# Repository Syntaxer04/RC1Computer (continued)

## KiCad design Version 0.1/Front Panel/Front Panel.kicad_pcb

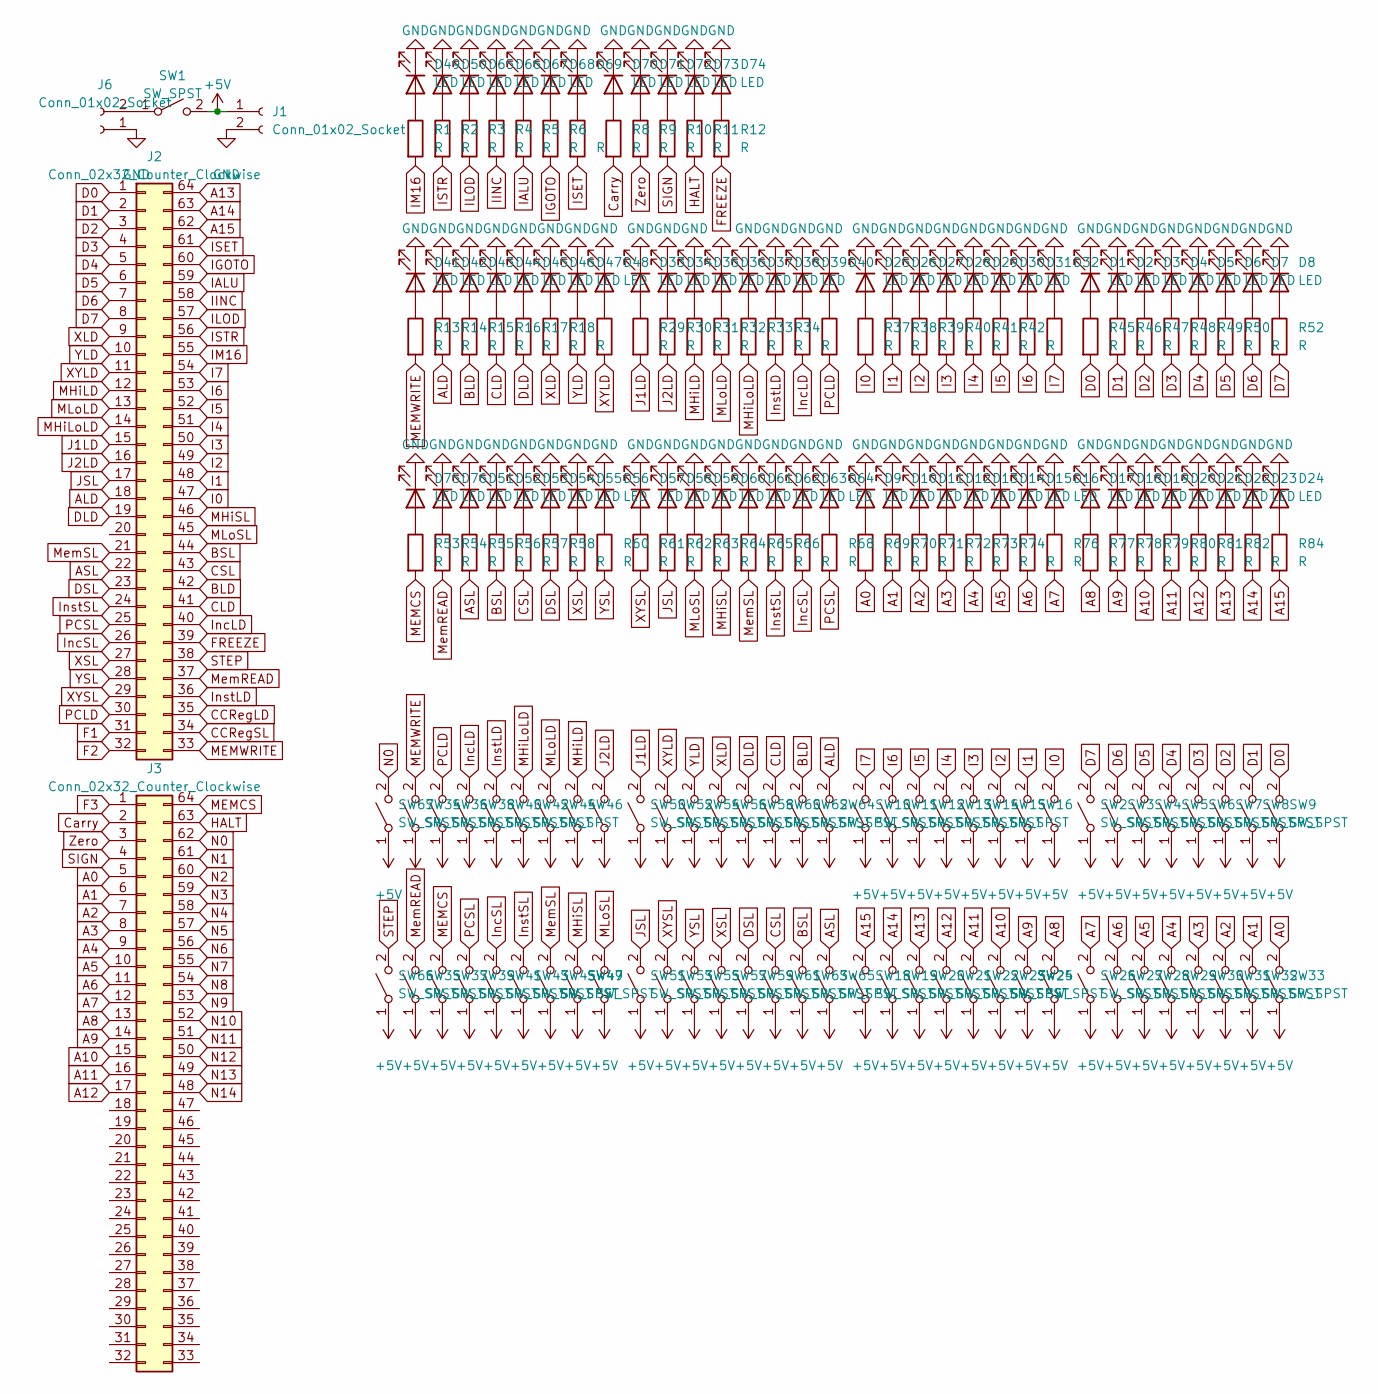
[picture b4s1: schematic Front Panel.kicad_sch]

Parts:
D1, D2, D3, D4, D5, D6, D7, D8, D9, D10, D11, D12, D13, D14, D15, D16, D17, D18, D19, D20, D21, D22, D23, D24, D25, D26, D27, D28, D29, D30, D31, D32, D33, D34, D35, D36, D37, D38, D39, D40, D41, D42, D43, D44, D45, D46, D47, D48, D49, D50, D51, D52, D53, D54, D55, D56, D57, D58, D59, D60, D61, D62, D63, D64, D65, D66, D67, D68, D69, D70, D71, D72, D73, D74, D75, D76: LED; LED_D8.0mm
J1, J6: Conn_01x02_Socket; JWT_A3963_1x02_P3.96mm_Vertical
J2, J3: Conn_02x32_Counter_Clockwise; IDC-Header_2x32_P2.54mm_Vertical
R1, R2, R3, R4, R5, R6, R7, R8, R9, R10, R11, R12, R13, R14, R15, R16, R17, R18, R19, R20, R29, R30, R31, R32, R33, R34, R35, R36, R37, R38, R39, R40, R41, R42, R43, R44, R45, R46, R47, R48, R49, R50, R51, R52, R53, R54, R55, R56, R57, R58, R59, R60, R61, R62, R63, R64, R65, R66, R67, R68, R69, R70, R71, R72, R73, R74, R75, R76, R77, R78, R79, R80, R81, R82, R83, R84: R; R_Axial_DIN0204_L3.6mm_D1.6mm_P2.54mm_Vertical
SW1, SW2, SW3, SW4, SW5, SW6, SW7, SW8, SW9, SW10, SW11, SW12, SW13, SW14, SW15, SW16, SW17, SW18, SW19, SW20, SW21, SW22, SW23, SW24, SW25, SW26, SW27, SW28, SW29, SW30, SW31, SW32, SW33, SW34, SW35, SW36, SW37, SW38, SW39, SW40, SW41, SW42, SW43, SW44, SW45, SW46, SW47, SW48, SW49, SW50, SW51, SW52, SW53, SW54, SW55, SW56, SW57, SW58, SW59, SW60, SW61, SW62, SW63, SW64, SW65, SW66, SW67: SW_SPST; Switches

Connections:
+5V: J1.1, SW1.2 (B), SW2.1 (A), SW3.1 (A), SW4.1 (A), SW5.1 (A), SW6.1 (A), SW7.1 (A), SW8.1 (A), SW9.1 (A), SW10.1 (A), SW11.1 (A), SW12.1 (A), SW13.1 (A), SW14.1 (A), SW15.1 (A), SW16.1 (A), SW17.1 (A), SW18.1 (A), SW19.1 (A), SW20.1 (A), SW21.1 (A), SW22.1 (A), SW23.1 (A), SW24.1 (A), SW25.1 (A), SW26.1 (A), SW27.1 (A), SW28.1 (A), SW29.1 (A), SW30.1 (A), SW31.1 (A), SW32.1 (A), SW33.1 (A), SW34.1 (A), SW35.1 (A), SW36.1 (A), SW37.1 (A), SW38.1 (A), SW39.1 (A), SW40.1 (A), SW41.1 (A), SW42.1 (A), SW43.1 (A), SW44.1 (A), SW45.1 (A), SW46.1 (A), SW47.1 (A), SW48.1 (A), SW49.1 (A), SW50.1 (A), SW51.1 (A), SW52.1 (A), SW53.1 (A), SW54.1 (A), SW55.1 (A), SW56.1 (A), SW57.1 (A), SW58.1 (A), SW59.1 (A), SW60.1 (A), SW61.1 (A), SW62.1 (A), SW63.1 (A), SW64.1 (A), SW65.1 (A), SW66.1 (A), SW67.1 (A)
A0: J3.5, R69.2, SW33.2 (B)
A1: J3.6, R70.2, SW32.2 (B)
A2: J3.7, R71.2, SW31.2 (B)
A3: J3.8, R72.2, SW30.2 (B)
A4: J3.9, R73.2, SW29.2 (B)
A5: J3.10, R74.2, SW28.2 (B)
A6: J3.11, R75.2, SW27.2 (B)
A7: J3.12, R76.2, SW26.2 (B)
A8: J3.13, R77.2, SW25.2 (B)
A9: J3.14, R78.2, SW24.2 (B)
A10: J3.15, R79.2, SW23.2 (B)
A11: J3.16, R80.2, SW22.2 (B)
A12: J3.17, R81.2, SW21.2 (B)
A13: J2.64, R82.2, SW20.2 (B)
A14: J2.63, R83.2, SW19.2 (B)
A15: J2.62, R84.2, SW18.2 (B)
ALD: J2.18, R14.2, SW64.2 (B)
ASL: J2.22, R55.2, SW65.2 (B)
BLD: J2.42, R15.2, SW62.2 (B)
BSL: J2.44, R56.2, SW63.2 (B)
CCRegLD: J2.35
CCRegSL: J2.34
CLD: J2.41, R16.2, SW60.2 (B)
CSL: J2.43, R57.2, SW61.2 (B)
Carry: J3.2, R8.2
D0: J2.1, R45.2, SW9.2 (B)
D1: J2.2, R46.2, SW8.2 (B)
D2: J2.3, R47.2, SW7.2 (B)
D3: J2.4, R48.2, SW6.2 (B)
D4: J2.5, R49.2, SW5.2 (B)
D5: J2.6, R50.2, SW4.2 (B)
D6: J2.7, R51.2, SW3.2 (B)
D7: J2.8, R52.2, SW2.2 (B)
DLD: J2.19, R17.2, SW58.2 (B)
DSL: J2.23, R58.2, SW59.2 (B)
F1: J2.31
F2: J2.32
F3: J3.1
FREEZE: J2.39, R12.2
GND: D1.1 (K), D2.1 (K), D3.1 (K), D4.1 (K), D5.1 (K), D6.1 (K), D7.1 (K), D8.1 (K), D9.1 (K), D10.1 (K), D11.1 (K), D12.1 (K), D13.1 (K), D14.1 (K), D15.1 (K), D16.1 (K), D17.1 (K), D18.1 (K), D19.1 (K), D20.1 (K), D21.1 (K), D22.1 (K), D23.1 (K), D24.1 (K), D25.1 (K), D26.1 (K), D27.1 (K), D28.1 (K), D29.1 (K), D30.1 (K), D31.1 (K), D32.1 (K), D33.1 (K), D34.1 (K), D35.1 (K), D36.1 (K), D37.1 (K), D38.1 (K), D39.1 (K), D40.1 (K), D41.1 (K), D42.1 (K), D43.1 (K), D44.1 (K), D45.1 (K), D46.1 (K), D47.1 (K), D48.1 (K), D49.1 (K), D50.1 (K), D51.1 (K), D52.1 (K), D53.1 (K), D54.1 (K), D55.1 (K), D56.1 (K), D57.1 (K), D58.1 (K), D59.1 (K), D60.1 (K), D61.1 (K), D62.1 (K), D63.1 (K), D64.1 (K), D65.1 (K), D66.1 (K), D67.1 (K), D68.1 (K), D69.1 (K), D70.1 (K), D71.1 (K), D72.1 (K), D73.1 (K), D74.1 (K), D75.1 (K), D76.1 (K), J1.2, J6.1
HALT: J3.63, R11.2
I0: J2.47, R37.2, SW17.2 (B)
I1: J2.48, R38.2, SW16.2 (B)
I2: J2.49, R39.2, SW15.2 (B)
I3: J2.50, R40.2, SW14.2 (B)
I4: J2.51, R41.2, SW13.2 (B)
I5: J2.52, R42.2, SW12.2 (B)
I6: J2.53, R43.2, SW11.2 (B)
I7: J2.54, R44.2, SW10.2 (B)
IALU: J2.59, R5.2
IGOTO: J2.60, R6.2
IINC: J2.58, R4.2
ILOD: J2.57, R3.2
IM16: J2.55, R1.2
ISET: J2.61, R7.2
ISTR: J2.56, R2.2
IncLD: J2.40, R35.2, SW38.2 (B)
IncSL: J2.26, R67.2, SW41.2 (B)
InstLD: J2.36, R34.2, SW40.2 (B)
InstSL: J2.24, R66.2, SW43.2 (B)
J1LD: J2.15, R29.2, SW50.2 (B)
J2LD: J2.16, R30.2, SW48.2 (B)
JSL: J2.17, R62.2, SW51.2 (B)
MEMCS: J3.64, R53.2, SW37.2 (B)
MEMWRITE: J2.33, R13.2, SW34.2 (B)
MHiLD: J2.12, R31.2, SW46.2 (B)
MHiLoLD: J2.14, R33.2, SW42.2 (B)
MHiSL: J2.46, R64.2, SW47.2 (B)
MLoLD: J2.13, R32.2, SW44.2 (B)
MLoSL: J2.45, R63.2, SW49.2 (B)
MemREAD: J2.37, R54.2, SW35.2 (B)
MemSL: J2.21, R65.2, SW45.2 (B)
N0: J3.62, SW67.2 (B)
N1: J3.61
N2: J3.60
N3: J3.59
N4: J3.58
N5: J3.57
N6: J3.56
N7: J3.55
N8: J3.54
N9: J3.53
N10: J3.52
N11: J3.51
N12: J3.50
N13: J3.49
N14: J3.48
unnamed: D1.2 (A), R45.1
unnamed: D2.2 (A), R46.1
unnamed: D3.2 (A), R47.1
unnamed: D4.2 (A), R48.1
unnamed: D5.2 (A), R49.1
unnamed: D6.2 (A), R50.1
unnamed: D7.2 (A), R51.1
unnamed: D8.2 (A), R52.1
unnamed: D9.2 (A), R69.1
unnamed: D10.2 (A), R70.1
unnamed: D11.2 (A), R71.1
unnamed: D12.2 (A), R72.1
unnamed: D13.2 (A), R73.1
unnamed: D14.2 (A), R74.1
unnamed: D15.2 (A), R75.1
unnamed: D16.2 (A), R76.1
unnamed: D17.2 (A), R77.1
unnamed: D18.2 (A), R78.1
unnamed: D19.2 (A), R79.1
unnamed: D20.2 (A), R80.1
unnamed: D21.2 (A), R81.1
unnamed: D22.2 (A), R82.1
unnamed: D23.2 (A), R83.1
unnamed: D24.2 (A), R84.1
unnamed: D25.2 (A), R37.1
unnamed: D26.2 (A), R38.1
unnamed: D27.2 (A), R39.1
unnamed: D28.2 (A), R40.1
unnamed: D29.2 (A), R41.1
unnamed: D30.2 (A), R42.1
unnamed: D31.2 (A), R43.1
unnamed: D32.2 (A), R44.1
unnamed: D33.2 (A), R29.1
unnamed: D34.2 (A), R30.1
unnamed: D35.2 (A), R31.1
unnamed: D36.2 (A), R32.1
unnamed: D37.2 (A), R33.1
unnamed: D38.2 (A), R34.1
unnamed: D39.2 (A), R35.1
unnamed: D40.2 (A), R36.1
unnamed: D41.2 (A), R13.1
unnamed: D42.2 (A), R14.1
unnamed: D43.2 (A), R15.1
unnamed: D44.2 (A), R16.1
unnamed: D45.2 (A), R17.1
unnamed: D46.2 (A), R18.1
unnamed: D47.2 (A), R19.1
unnamed: D48.2 (A), R20.1
unnamed: D49.2 (A), R1.1
unnamed: D50.2 (A), R2.1
unnamed: D51.2 (A), R55.1
unnamed: D52.2 (A), R56.1
unnamed: D53.2 (A), R57.1
unnamed: D54.2 (A), R58.1
unnamed: D55.2 (A), R59.1
unnamed: D56.2 (A), R60.1
unnamed: D57.2 (A), R61.1
unnamed: D58.2 (A), R62.1
unnamed: D59.2 (A), R63.1
unnamed: D60.2 (A), R64.1
unnamed: D61.2 (A), R65.1
unnamed: D62.2 (A), R66.1
unnamed: D63.2 (A), R67.1
unnamed: D64.2 (A), R68.1
unnamed: D65.2 (A), R3.1
unnamed: D66.2 (A), R4.1
unnamed: D67.2 (A), R5.1
unnamed: D68.2 (A), R6.1
unnamed: D69.2 (A), R7.1
unnamed: D70.2 (A), R8.1
unnamed: D71.2 (A), R9.1
unnamed: D72.2 (A), R10.1
unnamed: D73.2 (A), R11.1
unnamed: D74.2 (A), R12.1
unnamed: D75.2 (A), R53.1
unnamed: D76.2 (A), R54.1
unnamed: J6.2, SW1.1 (A)
PCLD: J2.30, R36.2, SW36.2 (B)
PCSL: J2.25, R68.2, SW39.2 (B)
SIGN: J3.4, R10.2
STEP: J2.38, SW66.2 (B)
XLD: J2.9, R18.2, SW56.2 (B)
XSL: J2.27, R59.2, SW57.2 (B)
XYLD: J2.11, R20.2, SW52.2 (B)
XYSL: J2.29, R61.2, SW53.2 (B)
YLD: J2.10, R19.2, SW54.2 (B)
YSL: J2.28, R60.2, SW55.2 (B)
Zero: J3.3, R9.2

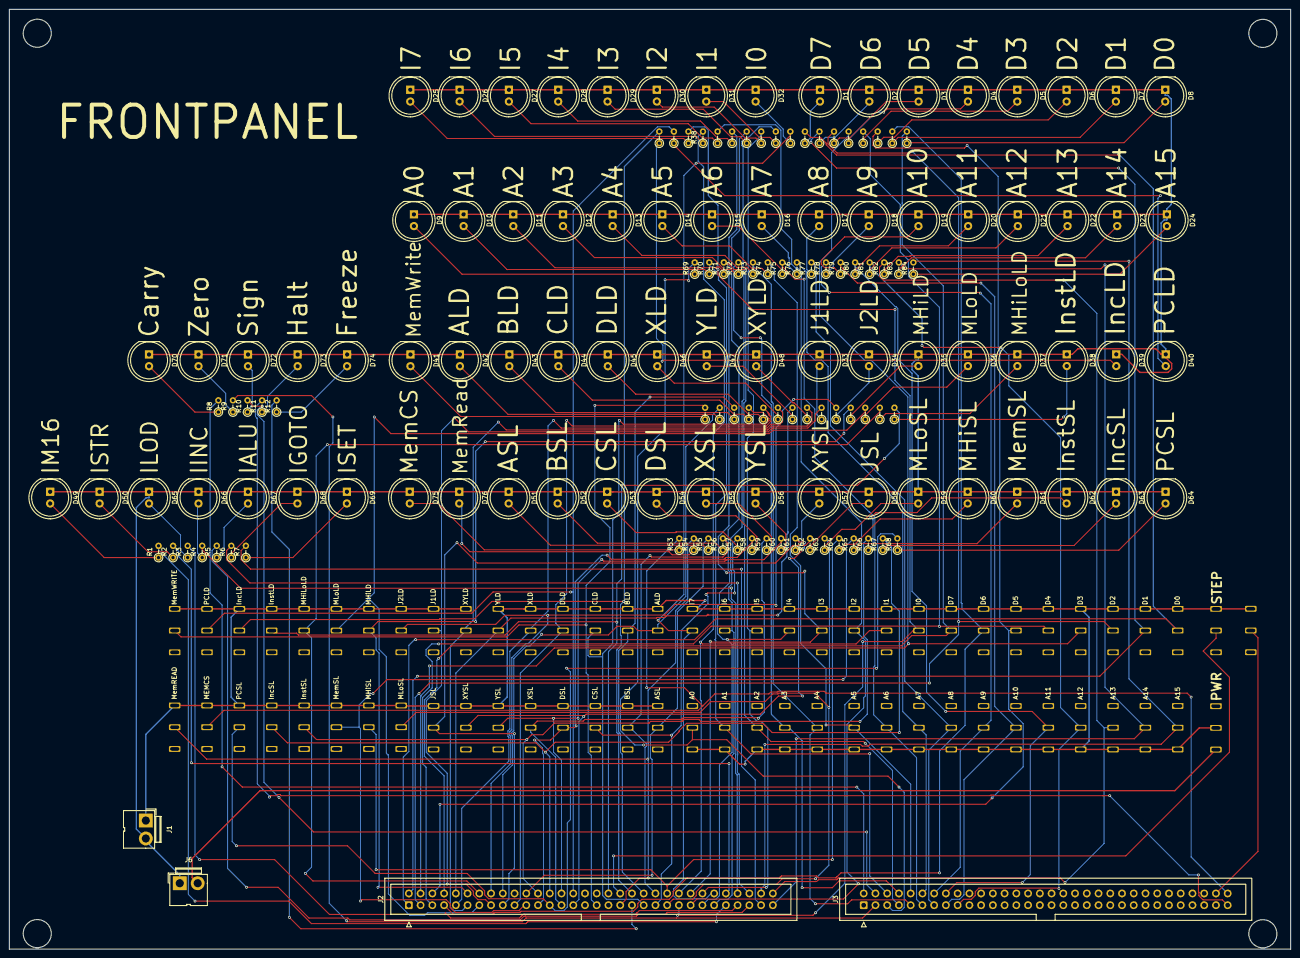
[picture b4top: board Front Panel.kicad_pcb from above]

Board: 2 copper layers, 277.2 x 203.3 mm, 223 parts (0 on the bottom side), 157 nets.

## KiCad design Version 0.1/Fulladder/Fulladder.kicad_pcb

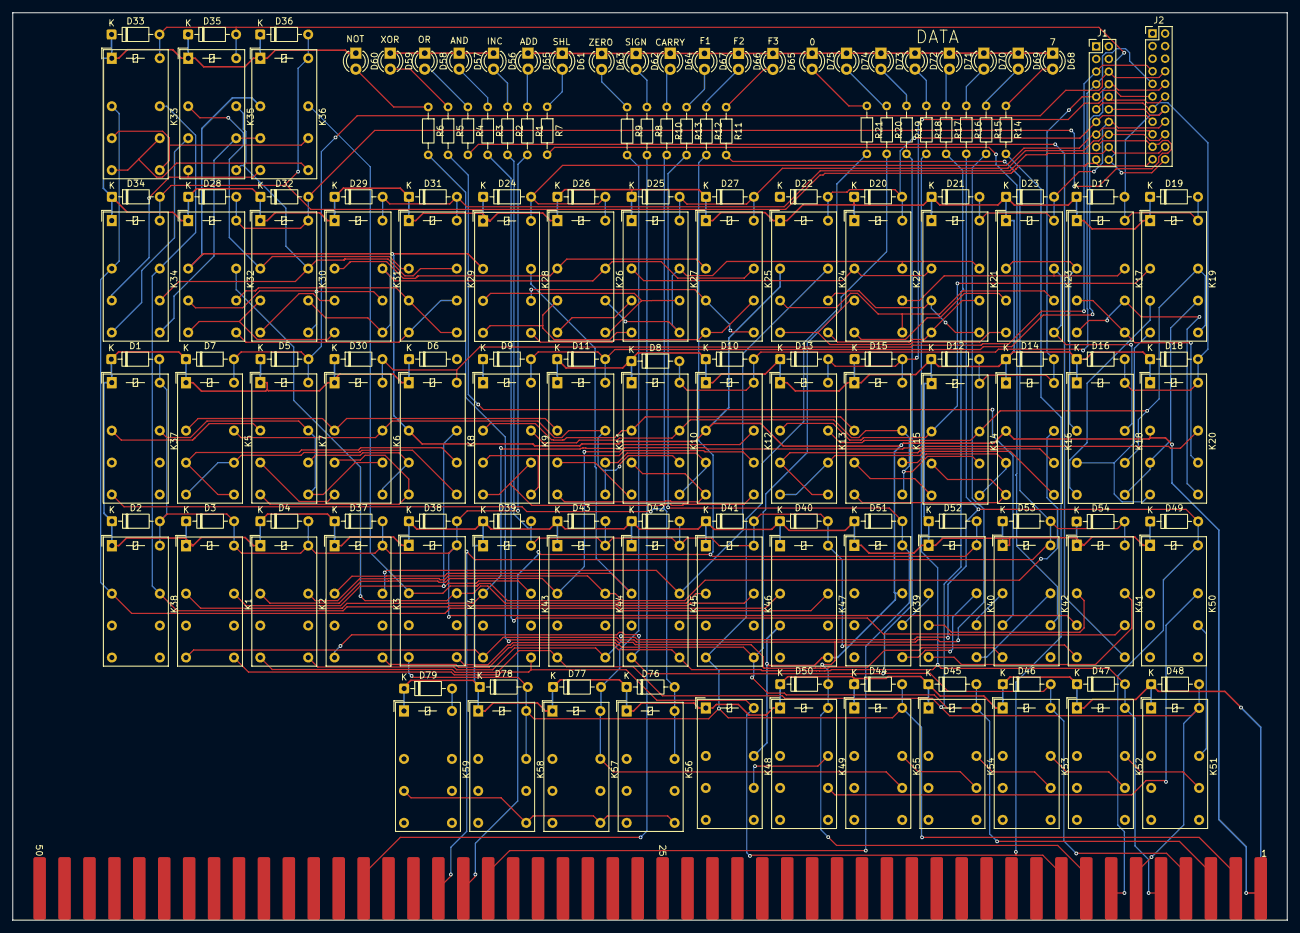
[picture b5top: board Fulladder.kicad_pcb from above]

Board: 2 copper layers, 202.5 x 144.2 mm, 162 parts (0 on the bottom side), 142 nets.

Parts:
D1, D2, D3, D4, D5, D6, D7, D8, D9, D10, D11, D12, D13, D14, D15, D16, D17, D18, D19, D20, D21, D22, D23, D24, D25, D26, D27, D28, D29, D30, D31, D32, D33, D34, D35, D36, D37, D38, D39, D40, D41, D42, D43, D44, D45, D46, D47, D48, D49, D50, D51, D52, D53, D54, D76, D77, D78, D79: 1N914; D_DO-35_SOD27_P7.62mm_Horizontal
D55, D56, D57, D58, D59, D60, D61, D62, D63, D64, D65, D66, D67, D68, D69, D70, D71, D72, D73, D74, D75: LED; LED_D3.0mm
J1: Conn_02x10_Odd_Even; PinHeader_2x10_P2.00mm_Vertical
J2: Conn_02x11_Odd_Even; PinHeader_2x11_P2.00mm_Vertical
K1, K2, K3, K4, K5, K6, K7, K8, K9, K10, K11, K12, K13, K14, K15, K16, K17, K18, K19, K20, K21, K22, K23, K24, K25, K26, K27, K28, K29, K30, K31, K32, K33, K34, K35, K36, K37, K38, K39, K40, K41, K42, K43, K44, K45, K46, K47, K48, K49, K50, K51, K52, K53, K54, K55, K56, K57, K58, K59: HK19F-DCxxV-SHC; Relay_DPDT_Finder_30.22
R1, R2, R3, R4, R5, R6, R7, R8, R9, R10, R11, R12, R13, R14, R15, R16, R17, R18, R19, R20, R21: R; R_Axial_DIN0204_L3.6mm_D1.6mm_P7.62mm_Horizontal
U1: Conn_RC_Male_100

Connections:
CCLD: D79.2 (A), K59.A2
Carry: D76.2 (A), K37.14, K56.21, K56.A2, R10.2
GND: D1.1 (K), D2.1 (K), D3.1 (K), D4.1 (K), D5.1 (K), D6.1 (K), D7.1 (K), D8.1 (K), D10.1 (K), D11.1 (K), D12.1 (K), D13.1 (K), D14.1 (K), D15.1 (K), D16.1 (K), D17.1 (K), D18.1 (K), D19.1 (K), D20.1 (K), D21.1 (K), D23.1 (K), D24.1 (K), D25.1 (K), D26.1 (K), D27.1 (K), D28.1 (K), D29.1 (K), D30.1 (K), D31.1 (K), D32.1 (K), D33.1 (K), D34.1 (K), D35.1 (K), D36.1 (K), D37.1 (K), D38.1 (K), D39.1 (K), D40.1 (K), D41.1 (K), D42.1 (K), D43.1 (K), D44.1 (K), D45.1 (K), D46.1 (K), D47.1 (K), D48.1 (K), D49.1 (K), D50.1 (K), D51.1 (K), D52.1 (K), D53.1 (K), D54.1 (K), D55.1 (K), D56.1 (K), D57.1 (K), D58.1 (K), D59.1 (K), D60.1 (K), D61.1 (K), D62.1 (K), D63.1 (K), D64.1 (K), D65.1 (K), D66.1 (K), D67.1 (K), D68.1 (K), D69.1 (K), D70.1 (K), D71.1 (K), D72.1 (K), D73.1 (K), D74.1 (K), D75.1 (K), D76.1 (K), D77.1 (K), D78.1 (K), D79.1 (K), K1.A1, K2.A1, K3.A1, K4.A1, K5.A1, K6.A1, K7.A1, K8.A1, K10.A1, K11.A1, K12.A1, K13.A1, K14.A1, K15.A1, K16.A1, K17.A1, K18.A1, K19.A1, K20.A1, K21.A1, K22.A1, K23.A1, K24.A1, K25.A1, K26.A1, K27.A1, K28.A1, K29.A1, K30.A1, K31.A1, K32.A1, K33.A1, K34.A1, K35.A1, K36.A1, K37.A1, K38.A1, K39.A1, K40.A1, K41.A1, K42.A1, K43.A1, K44.A1, K45.A1, K46.A1, K47.A1, K48.A1, K49.A1, K50.A1, K51.A1, K52.A1, K53.A1, K54.A1, K55.A1, K56.A1, K57.A1, K58.A1, K59.A1, U1.51 (GND)
unnamed: D1.2 (A), D2.2 (A), D3.2 (A), D4.2 (A), D37.2 (A), D38.2 (A), K1.A2, K2.A2, K3.A2, K4.A2, K37.A2, K38.A2, K41.12, R1.2
unnamed: D5.2 (A), D7.2 (A), J1.6, J2.8, K5.A2, K7.A2
unnamed: D9.1 (K), K9.A1
unnamed: D8.2 (A), D10.2 (A), J1.7, J2.9, K10.A2, K12.A2
unnamed: D9.2 (A), D11.2 (A), J1.8, J2.10, K9.A2, K11.A2
unnamed: D12.2 (A), D14.2 (A), J1.9, J2.11, K14.A2, K16.A2
unnamed: D13.2 (A), D15.2 (A), J1.10, J2.12, K13.A2, K15.A2
unnamed: D16.2 (A), D18.2 (A), J1.11, J2.13, K18.A2, K20.A2
unnamed: D17.2 (A), D19.2 (A), J1.12, J2.14, K17.A2, K19.A2
unnamed: D20.2 (A), D22.2 (A), J1.13, J2.15, K22.A2, K24.A2
unnamed: D21.2 (A), D23.2 (A), J1.14, J2.16, K21.A2, K23.A2
unnamed: D24.2 (A), D26.2 (A), J1.15, J2.17, K26.A2, K28.A2
unnamed: D25.2 (A), D27.2 (A), J1.16, J2.18, K25.A2, K27.A2
unnamed: D28.2 (A), D32.2 (A), J1.17, J2.19, K30.A2, K32.A2
unnamed: D29.2 (A), D31.2 (A), J1.18, J2.20, K29.A2, K31.A2
unnamed: D30.2 (A), J1.5, J2.7, K6.A2, K8.A2
unnamed: D33.2 (A), D35.2 (A), J1.20, J2.22, K33.A2, K35.A2
unnamed: D34.2 (A), D36.2 (A), J1.19, J2.21, K34.A2, K36.A2
unnamed: D39.2 (A), D40.2 (A), D41.2 (A), D42.2 (A), D43.2 (A), K41.14, K43.A2, K44.A2, K45.A2, K46.A2, K47.A2, R2.2
unnamed: D45.2 (A), K4.24, K46.24, K54.A2, R20.2, U1.3 (D1)
unnamed: D46.2 (A), K3.14, K45.14, K53.A2, R19.2, U1.4 (D2)
unnamed: D47.2 (A), K3.24, K45.24, K52.A2, R18.2, U1.5 (D3)
unnamed: D48.2 (A), K2.14, K44.14, K51.A2, R17.2, U1.6 (D4)
unnamed: D49.2 (A), K2.24, K44.24, K50.A2, R16.2, U1.7 (D5)
unnamed: D50.2 (A), K1.14, K43.14, K49.A2, R15.2, U1.8 (D6)
unnamed: D51.2 (A), K39.A2, R13.2, U1.32 (F1)
unnamed: D52.2 (A), K40.A2, R12.2, U1.33 (F2)
unnamed: D53.2 (A), D54.2 (A), K41.A2, K42.A2, R11.2, U1.34 (F3)
unnamed: D55.2 (A), R1.1
unnamed: D56.2 (A), R2.1
unnamed: D57.2 (A), R3.1
unnamed: D58.2 (A), R4.1
unnamed: D59.2 (A), R5.1
unnamed: D60.2 (A), R6.1
unnamed: D61.2 (A), R7.1
unnamed: D62.2 (A), R8.1
unnamed: D63.2 (A), R9.1
unnamed: D64.2 (A), R10.1
unnamed: D65.2 (A), R11.1
unnamed: D66.2 (A), R12.1
unnamed: D67.2 (A), R13.1
unnamed: D68.2 (A), R14.1
unnamed: D69.2 (A), R15.1
unnamed: D70.2 (A), R16.1
unnamed: D71.2 (A), R17.1
unnamed: D72.2 (A), R18.1
unnamed: D73.2 (A), R19.1
unnamed: D74.2 (A), R20.1
unnamed: D75.2 (A), R21.1
unnamed: K42.14, R6.2
unnamed: K42.12, R5.2
unnamed: K42.22, R7.2
unnamed: K41.24, R4.2
unnamed: K41.22, R3.2
unnamed: K1.11, K12.21, K43.11
unnamed: K1.21, K8.21, K43.21
unnamed: K2.11, K20.21, K44.11
unnamed: K5.12, K5.24, K8.22
unnamed: K5.14, K5.22, K8.24
unnamed: K6.12, K7.14, K8.14
unnamed: K6.14, K7.12
unnamed: K6.24, K7.22, K8.12
unnamed: K9.11, K10.11, K15.11
unnamed: K10.12, K11.14, K12.14
unnamed: K10.14, K11.12
unnamed: K9.21, K10.21, K14.22, K15.21, K15.24
unnamed: K5.21, K6.21, K10.22, K11.21, K11.24
unnamed: K10.24, K11.22, K12.12
unnamed: K5.11, K6.11, K11.11
unnamed: K9.12, K9.24, K12.22
unnamed: K9.14, K9.22, K12.24
unnamed: K13.11, K14.11, K19.11
unnamed: K13.12, K13.24, K16.22
unnamed: K13.14, K13.22, K16.24
unnamed: K13.21, K14.21, K18.22, K19.21, K19.24
unnamed: K14.12, K15.14, K16.14
unnamed: K14.14, K15.12
unnamed: K14.24, K15.22, K16.12
unnamed: K2.21, K16.21, K44.21
unnamed: K17.11, K18.11, K23.11
unnamed: K17.12, K17.24, K20.22
unnamed: K17.14, K17.22, K20.24
unnamed: K17.21, K18.21, K22.22, K23.21, K23.24
unnamed: K18.12, K19.14, K20.14
unnamed: K18.14, K19.12
unnamed: K18.24, K19.22, K20.12
unnamed: K21.11, K22.11, K27.11
unnamed: K21.12, K21.24, K24.22
unnamed: K21.14, K21.22, K24.24
unnamed: K21.21, K22.21, K26.22, K27.21, K27.24
unnamed: K22.12, K23.14, K24.14
unnamed: K22.14, K23.12
unnamed: K22.24, K23.22, K24.12
unnamed: K3.21, K24.21, K45.21
unnamed: K25.11, K26.11, K31.11
unnamed: K25.12, K25.24, K28.22
unnamed: K25.14, K25.22, K28.24
unnamed: K25.21, K26.21, K30.22, K31.21, K31.24
unnamed: K26.12, K27.14, K28.14
unnamed: K26.14, K27.12
unnamed: K26.24, K27.22, K28.12
unnamed: K3.11, K28.21, K45.11
unnamed: K29.11, K30.11, K35.11
unnamed: K29.12, K29.24, K32.22
unnamed: K29.14, K29.22, K32.24
unnamed: K29.21, K30.21, K34.22, K35.21, K35.24
unnamed: K30.12, K31.14, K32.14
unnamed: K30.14, K31.12
unnamed: K30.24, K31.22, K32.12
unnamed: K4.21, K32.21, K46.21
unnamed: K33.11, K34.11, K38.11, K47.21
unnamed: K33.12, K33.24, K36.22
unnamed: K33.14, K33.22, K36.24
unnamed: K33.21, K34.21, K38.21, K47.11
unnamed: K34.12, K35.14, K36.14
unnamed: K34.14, K35.12
unnamed: K34.24, K35.22, K36.12
unnamed: K4.11, K36.21, K46.11
unnamed: K7.11, K37.11
unnamed: K6.22, K7.21, K7.24, K37.21
unnamed: K39.22, K40.11
unnamed: K39.24, K40.21
unnamed: K40.12, K41.11
unnamed: K40.14, K41.21
unnamed: K40.22, K42.11
unnamed: K40.24, K42.21
unnamed: K48.22, K49.21
unnamed: K49.22, K50.21
unnamed: K50.22, K51.21
unnamed: K51.22, K52.21
unnamed: K52.22, K53.21
unnamed: K53.22, K54.21
unnamed: K54.22, K55.21
unnamed: K56.24, K57.24, K58.24, K59.12
unnamed: K8.11, K12.11, K16.11, K20.11, K24.11, K28.11, K32.11, K36.11, K39.21, K47.12, K47.24, K48.21, U1.1 (5_Volt)
unnamed: K1.24, K43.24, K48.A2, R14.2, U1.9 (D7)
unnamed: R8.2, U1.37 (SIGN)
Sign: D44.2 (A), D78.2 (A), K4.14, K46.14, K55.A2, K58.21, K58.A2, R21.2, U1.2 (D0)
Zero: D77.2 (A), K55.22, K57.21, K57.A2, R9.2
